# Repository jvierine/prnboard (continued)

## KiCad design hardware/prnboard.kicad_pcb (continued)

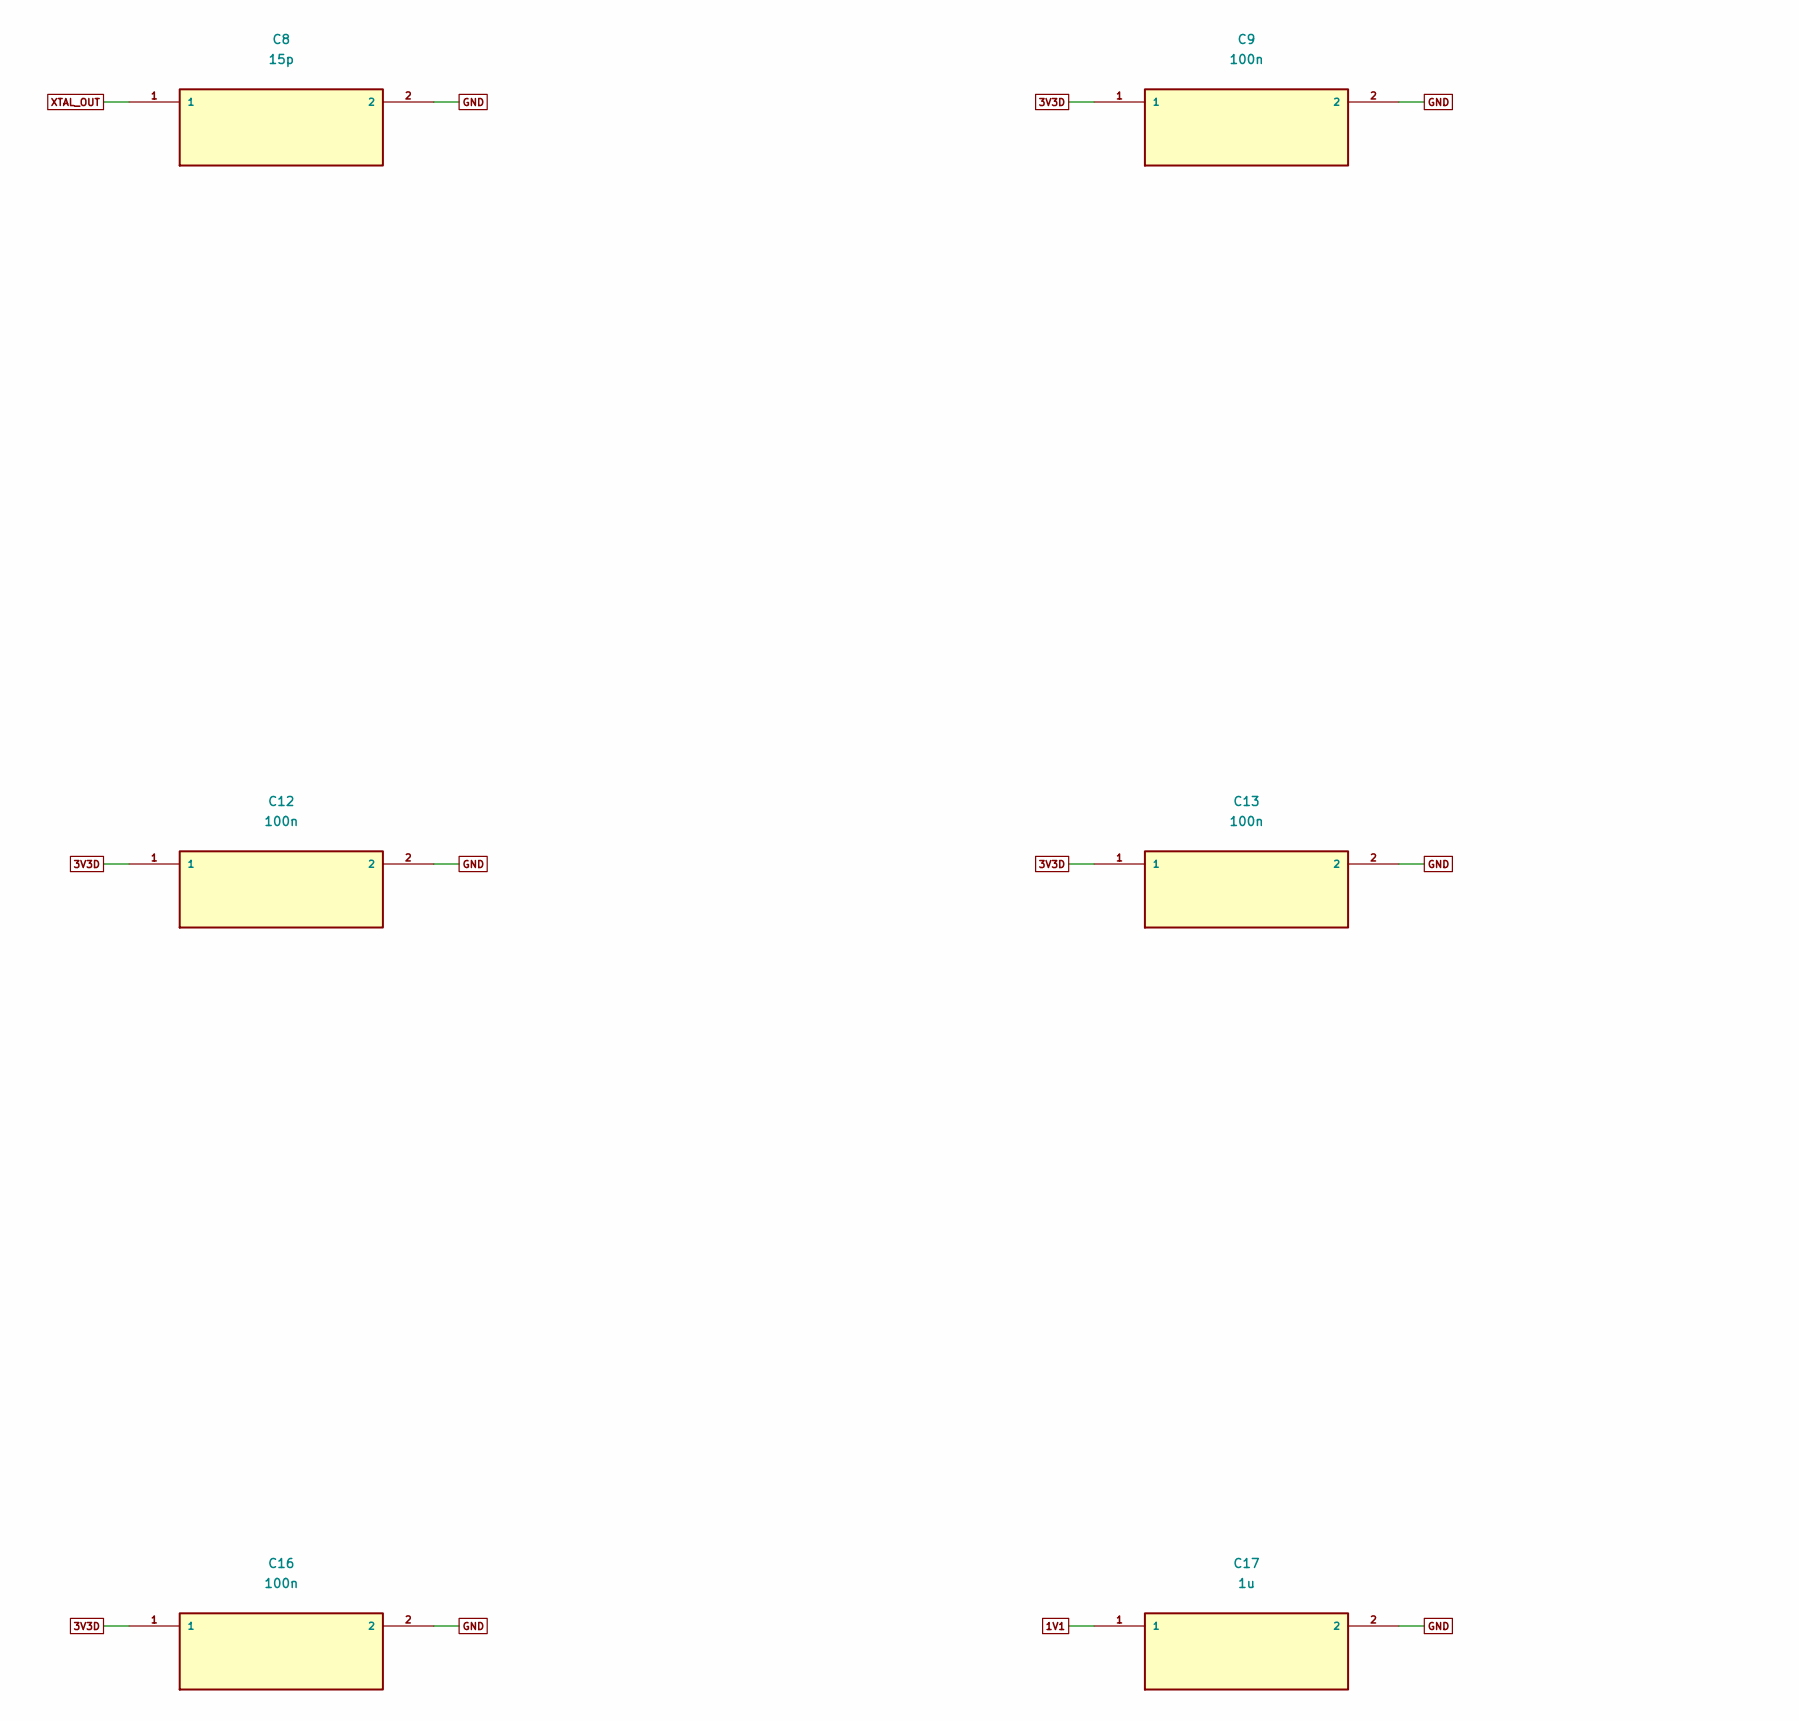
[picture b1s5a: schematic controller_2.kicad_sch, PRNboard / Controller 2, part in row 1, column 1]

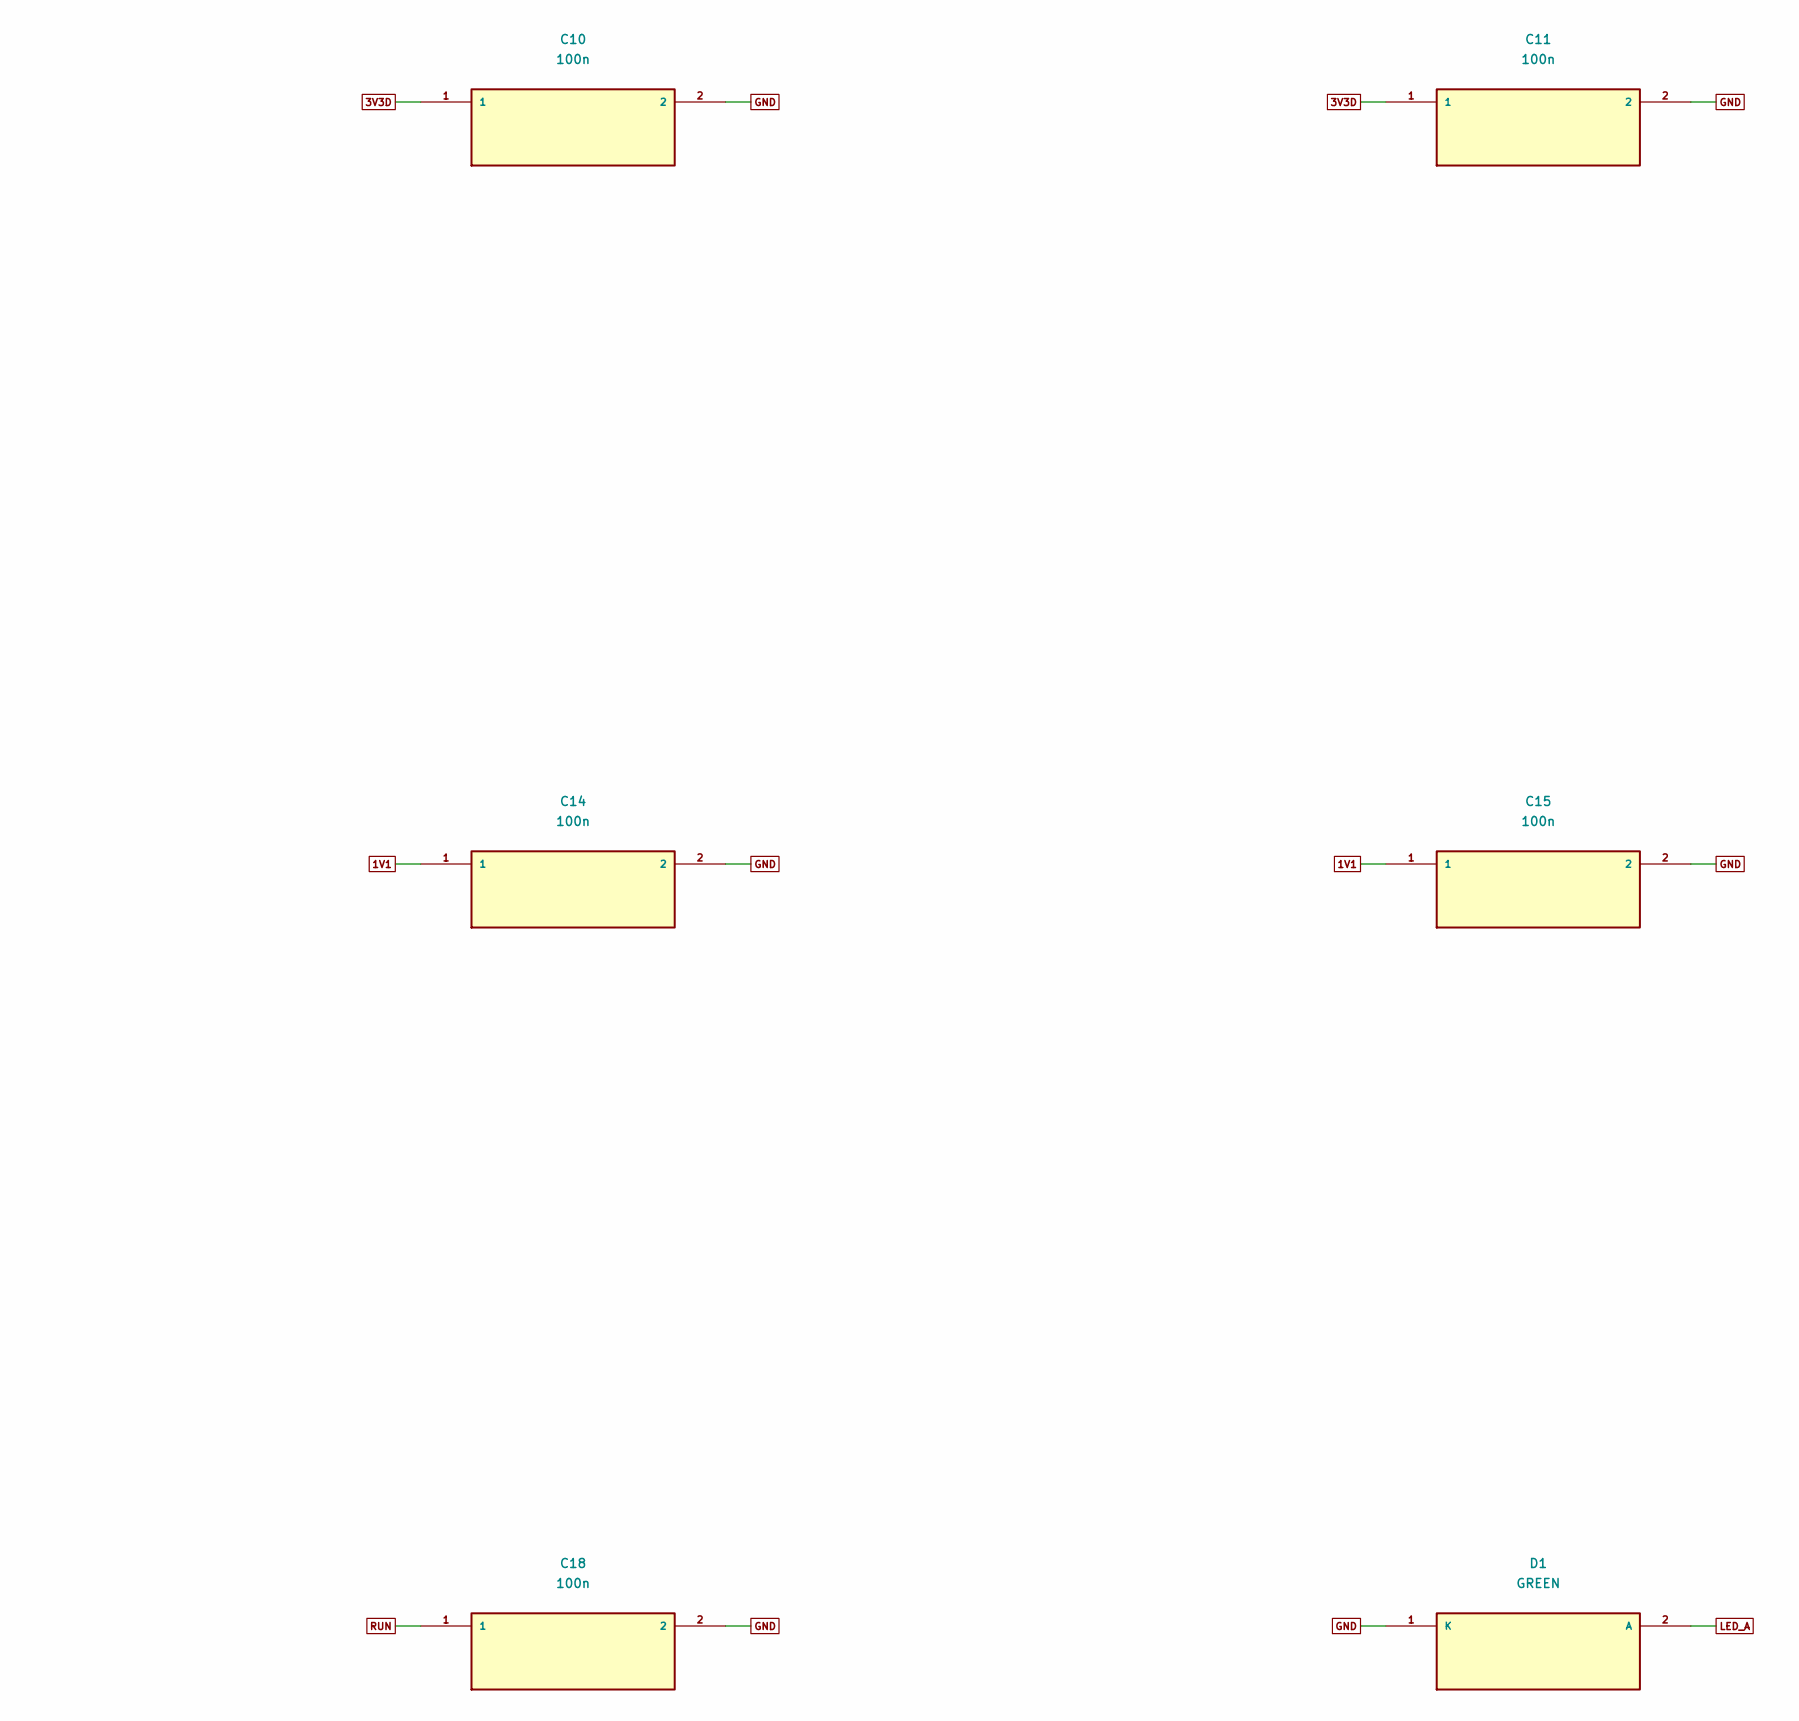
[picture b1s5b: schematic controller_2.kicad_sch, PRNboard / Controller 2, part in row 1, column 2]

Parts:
C8: 15p; C8; MPN SELECT_IN_BOM
C9: 100n; C9; MPN SELECT_IN_BOM
C10: 100n; C10; MPN SELECT_IN_BOM
C11: 100n; C11; MPN SELECT_IN_BOM
C12: 100n; C12; MPN SELECT_IN_BOM
C13: 100n; C13; MPN SELECT_IN_BOM
C14: 100n; C14; MPN SELECT_IN_BOM
C15: 100n; C15; MPN SELECT_IN_BOM
C16: 100n; C16; MPN SELECT_IN_BOM
C17: 1u; C17; MPN SELECT_IN_BOM
C18: 100n; C18; MPN SELECT_IN_BOM
D1: GREEN; D1; MPN GREEN

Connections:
1V1: C14.1, C15.1, C17.1; also elsewhere on the board
3V3D: C9.1, C10.1, C11.1, C12.1, C13.1, C16.1; also elsewhere on the board
GND: C8.2, C9.2, C10.2, C11.2, C12.2, C13.2, C14.2, C15.2, C16.2, C17.2, C18.2, D1.1 (K); also elsewhere on the board
LED_A: D1.2 (A); also elsewhere on the board
RUN: C18.1; also elsewhere on the board
XTAL_OUT: C8.1; also elsewhere on the board

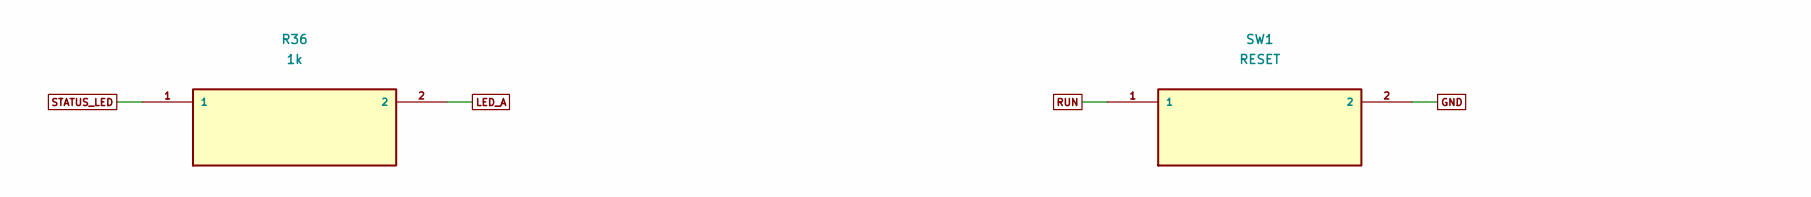
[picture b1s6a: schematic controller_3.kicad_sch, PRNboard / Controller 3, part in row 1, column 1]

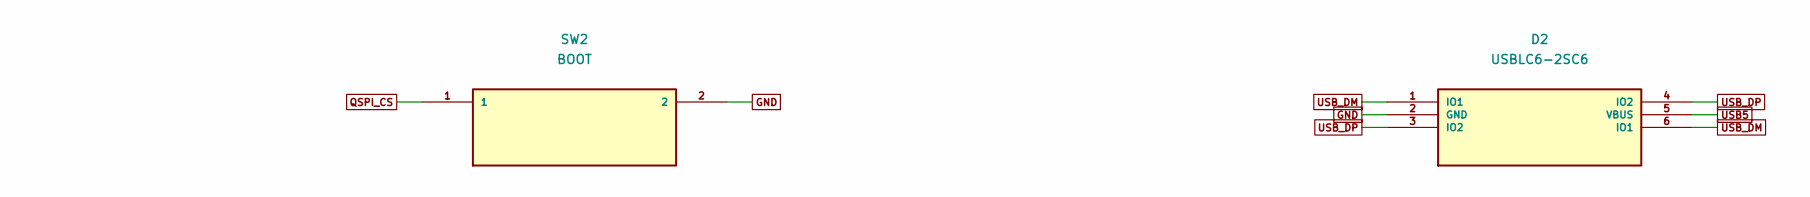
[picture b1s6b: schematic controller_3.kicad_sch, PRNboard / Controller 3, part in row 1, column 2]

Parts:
D2: USBLC6-2SC6; D2; MPN USBLC6-2SC6; LCSC C7519
R36: 1k; R36; MPN SELECT_IN_BOM
SW1: RESET; SW1; MPN TL3342F160QG
SW2: BOOT; SW2; MPN TL3342F160QG

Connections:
GND: D2.2 (GND), SW1.2, SW2.2; also elsewhere on the board
LED_A: R36.2; also elsewhere on the board
QSPI_CS: SW2.1; also elsewhere on the board
RUN: SW1.1; also elsewhere on the board
STATUS_LED: R36.1; also elsewhere on the board
USB5: D2.5 (VBUS); also elsewhere on the board
USB_DM: D2.1 (IO1), D2.6 (IO1); also elsewhere on the board
USB_DP: D2.3 (IO2), D2.4 (IO2); also elsewhere on the board

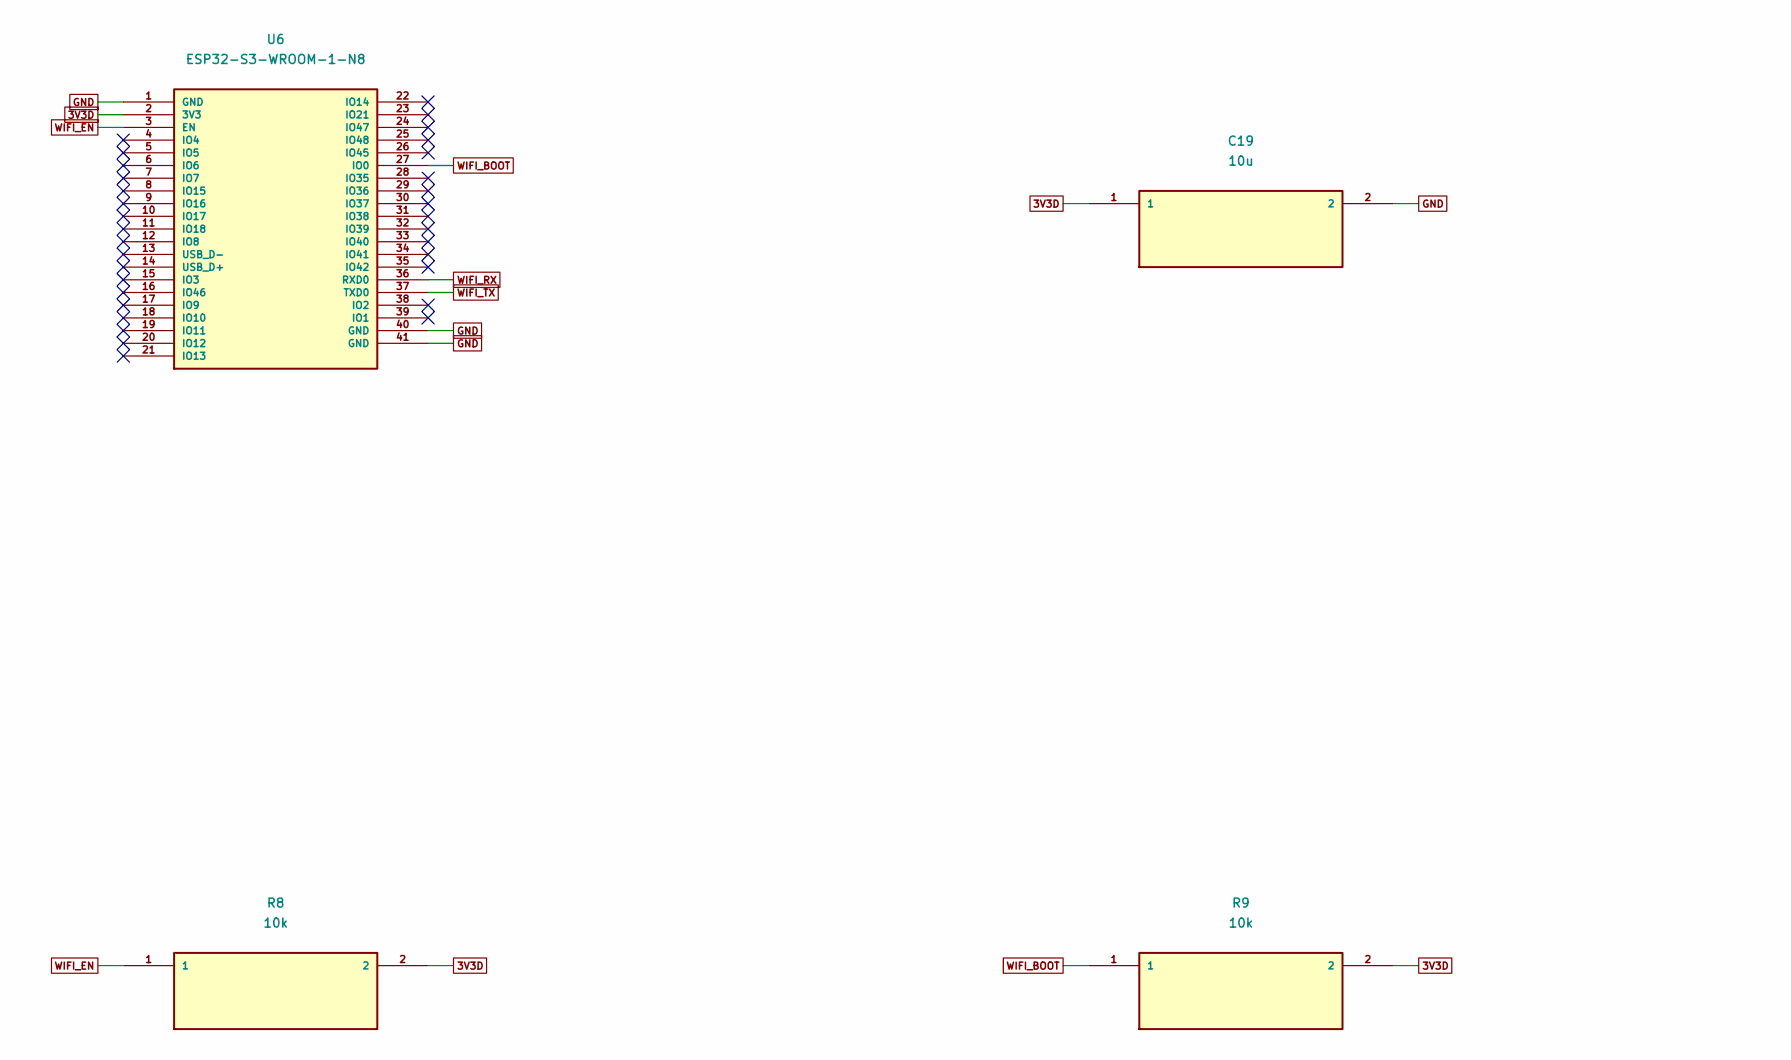
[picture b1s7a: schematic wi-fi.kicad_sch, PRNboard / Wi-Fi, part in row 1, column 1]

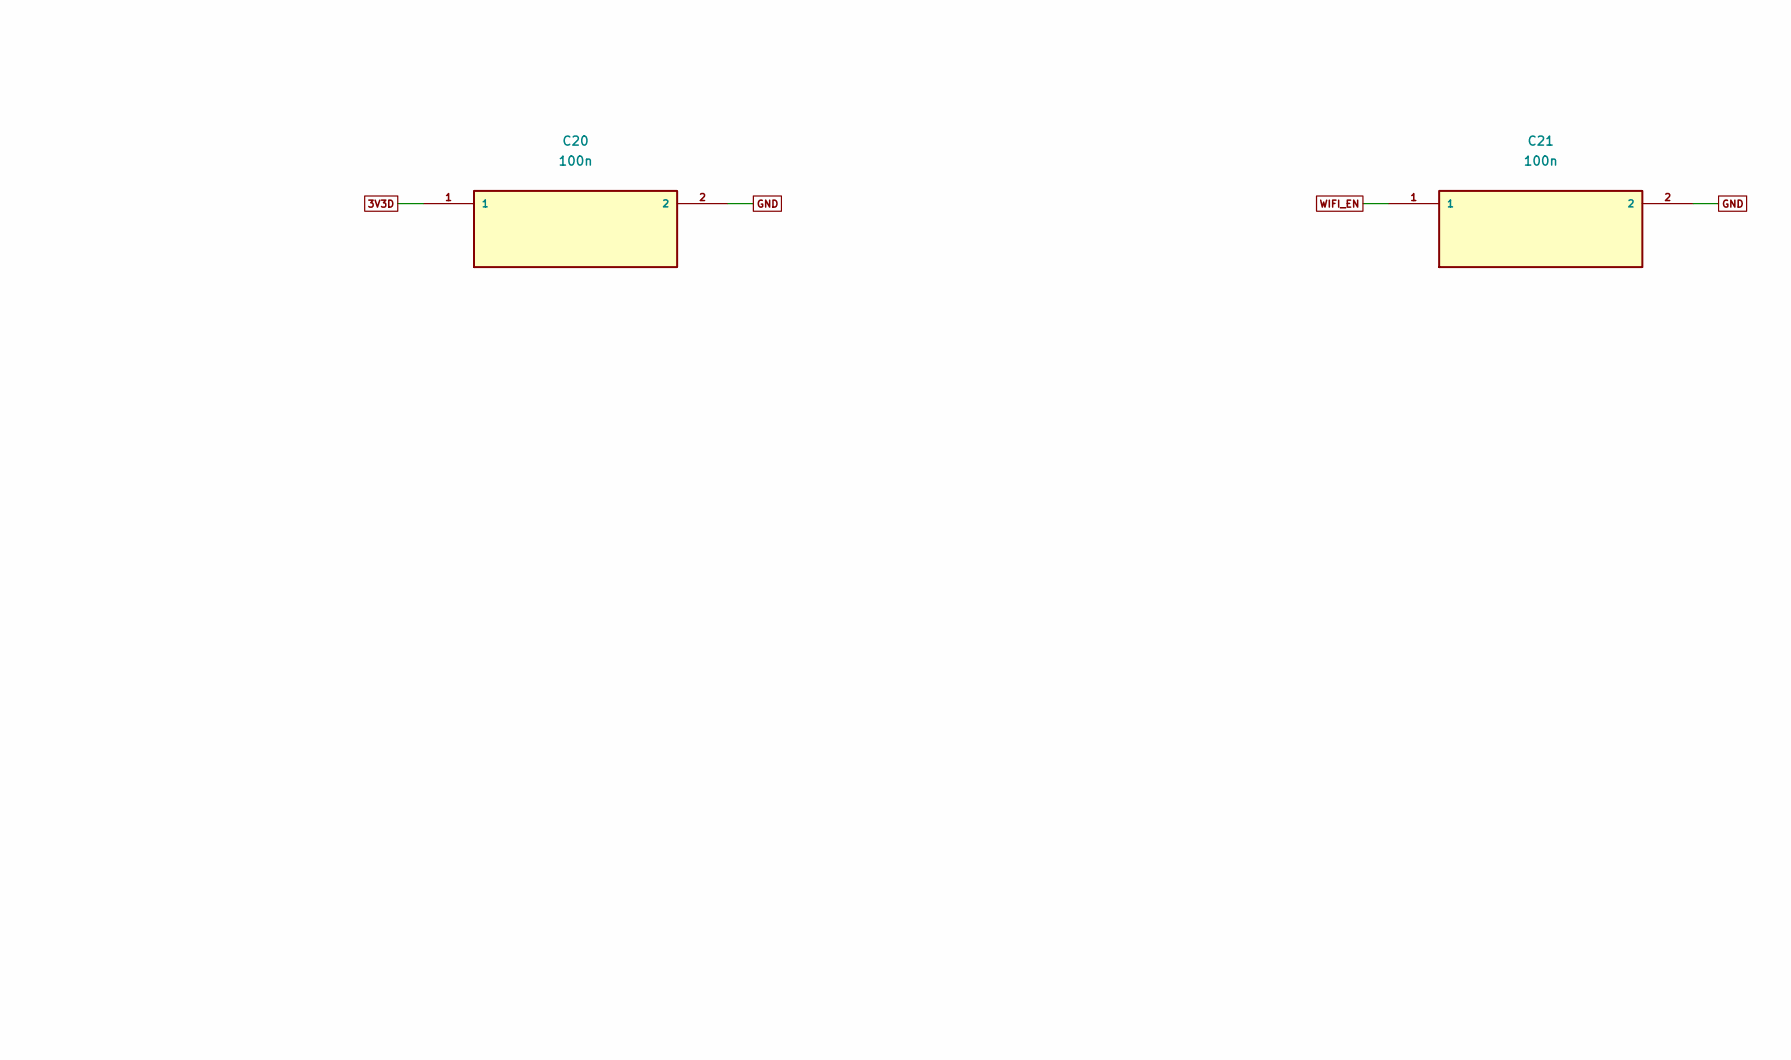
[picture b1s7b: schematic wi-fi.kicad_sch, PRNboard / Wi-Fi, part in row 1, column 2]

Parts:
C19: 10u; C19; MPN SELECT_IN_BOM
C20: 100n; C20; MPN SELECT_IN_BOM
C21: 100n; C21; MPN SELECT_IN_BOM
R8: 10k; R8; MPN SELECT_IN_BOM
R9: 10k; R9; MPN SELECT_IN_BOM
U6: ESP32-S3-WROOM-1-N8; U6; MPN ESP32-S3-WROOM-1-N8; LCSC C2913198

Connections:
3V3D: C19.1, C20.1, R8.2, R9.2, U6.2 (3V3); also elsewhere on the board
GND: C19.2, C20.2, C21.2, U6.1 (GND), U6.40 (GND), U6.41 (GND); also elsewhere on the board
WIFI_BOOT: R9.1, U6.27 (IO0); also elsewhere on the board
WIFI_EN: C21.1, R8.1, U6.3 (EN); also elsewhere on the board
WIFI_RX: U6.36 (RXD0); also elsewhere on the board
WIFI_TX: U6.37 (TXD0); also elsewhere on the board

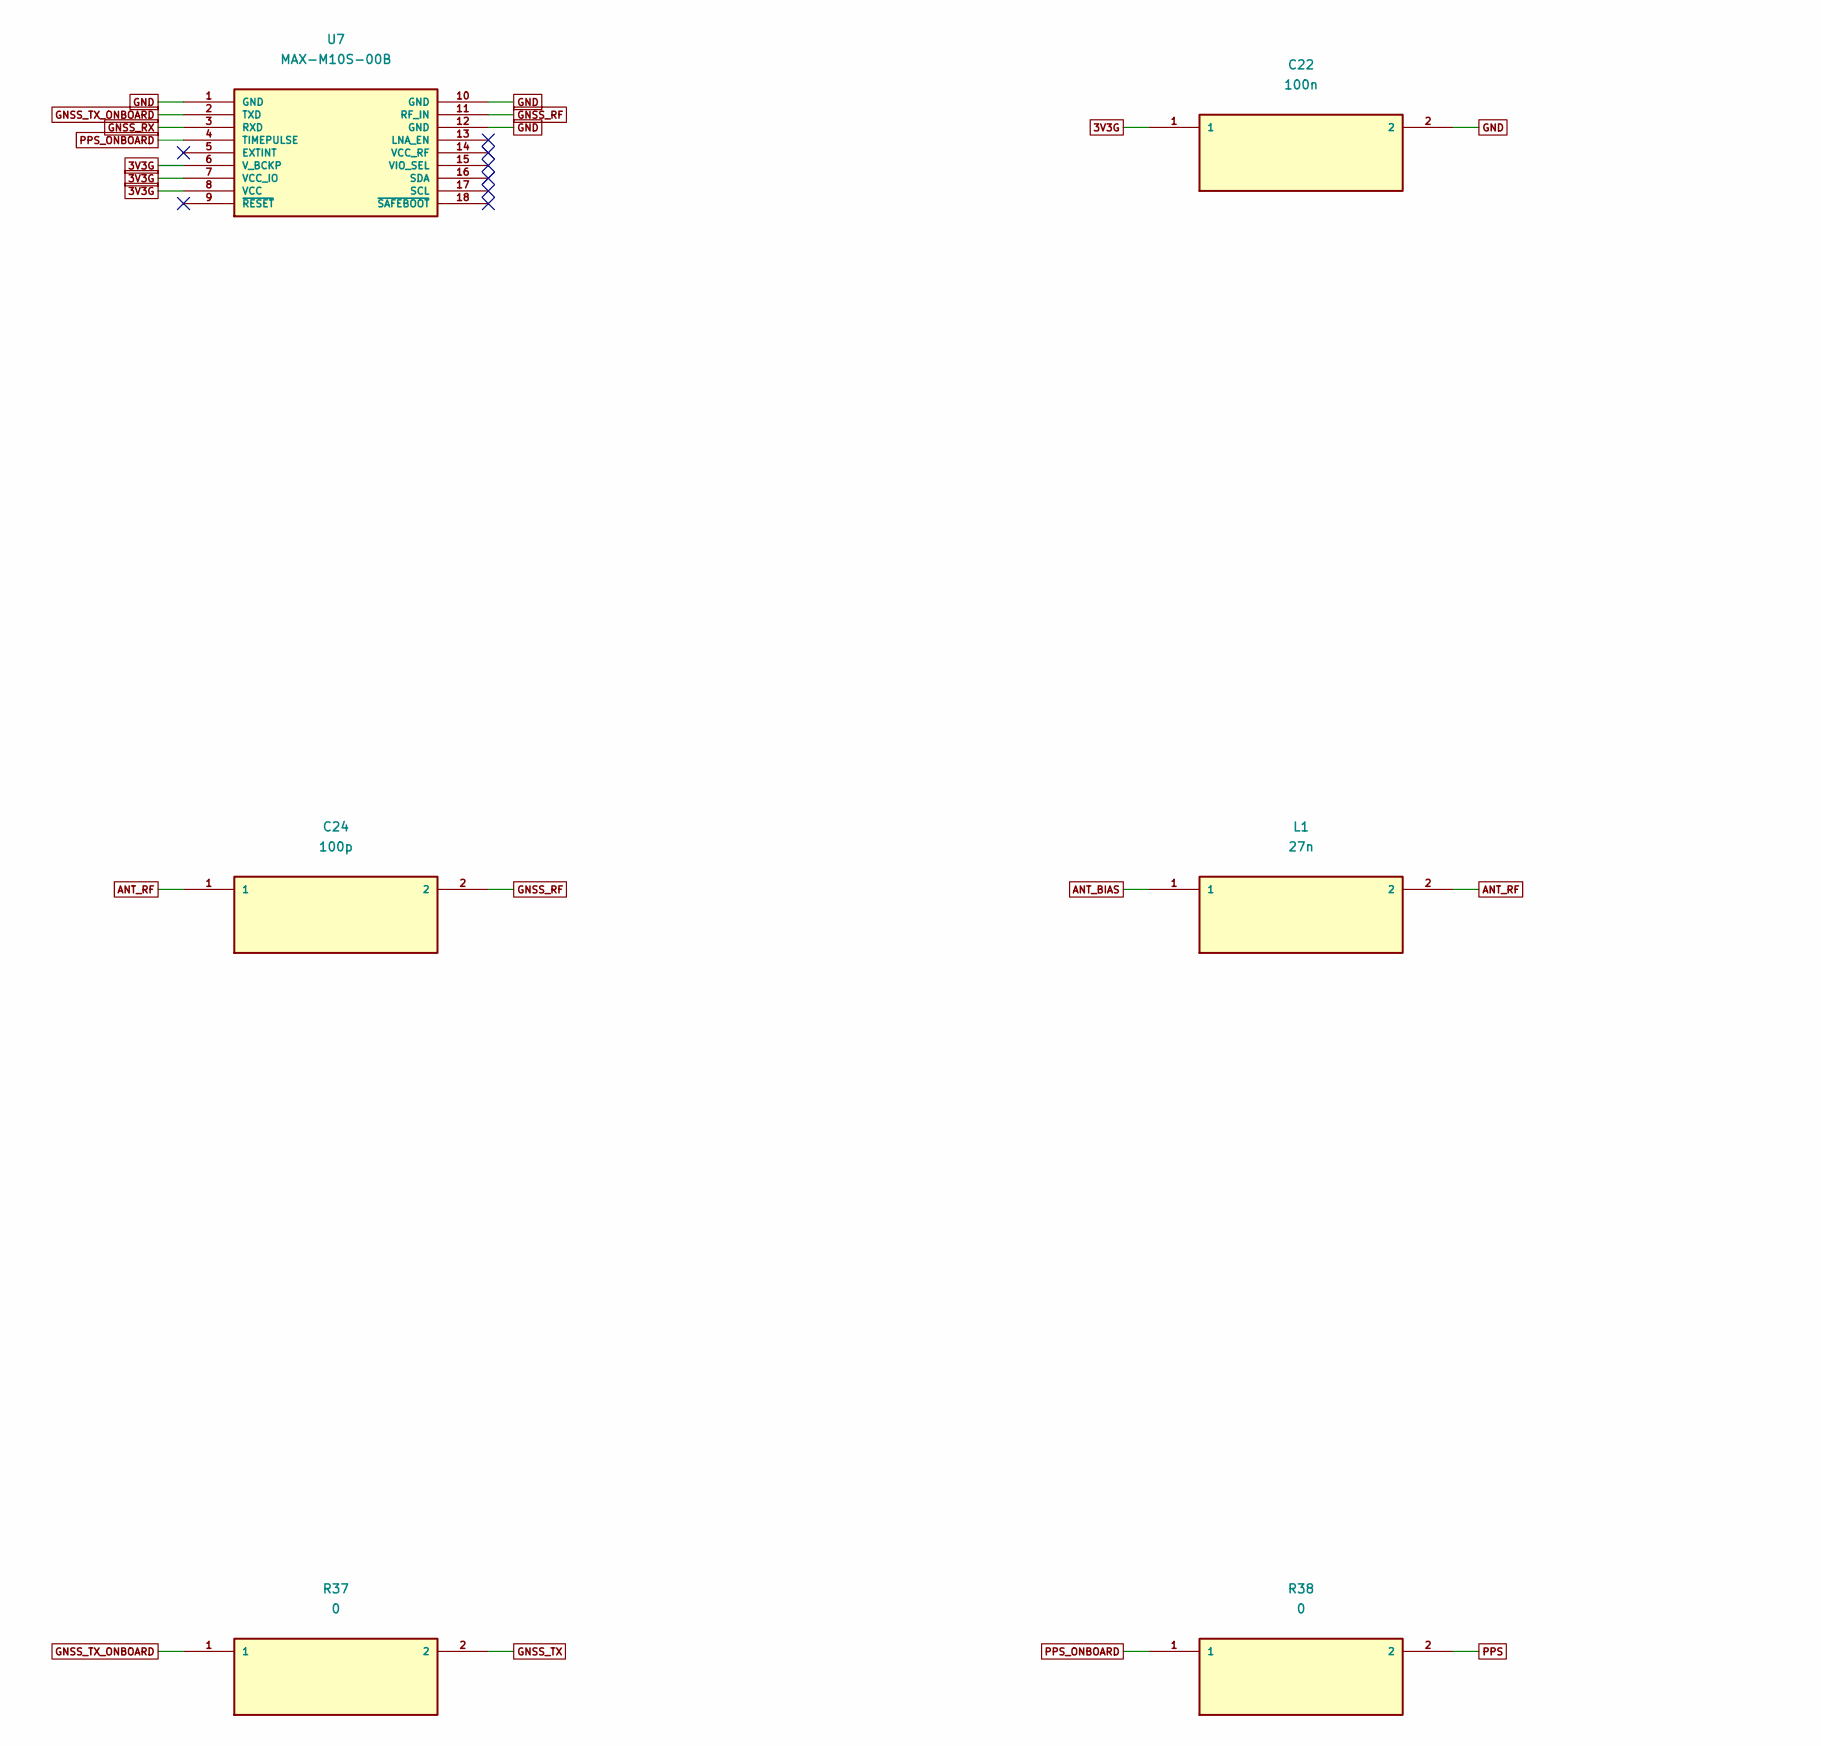
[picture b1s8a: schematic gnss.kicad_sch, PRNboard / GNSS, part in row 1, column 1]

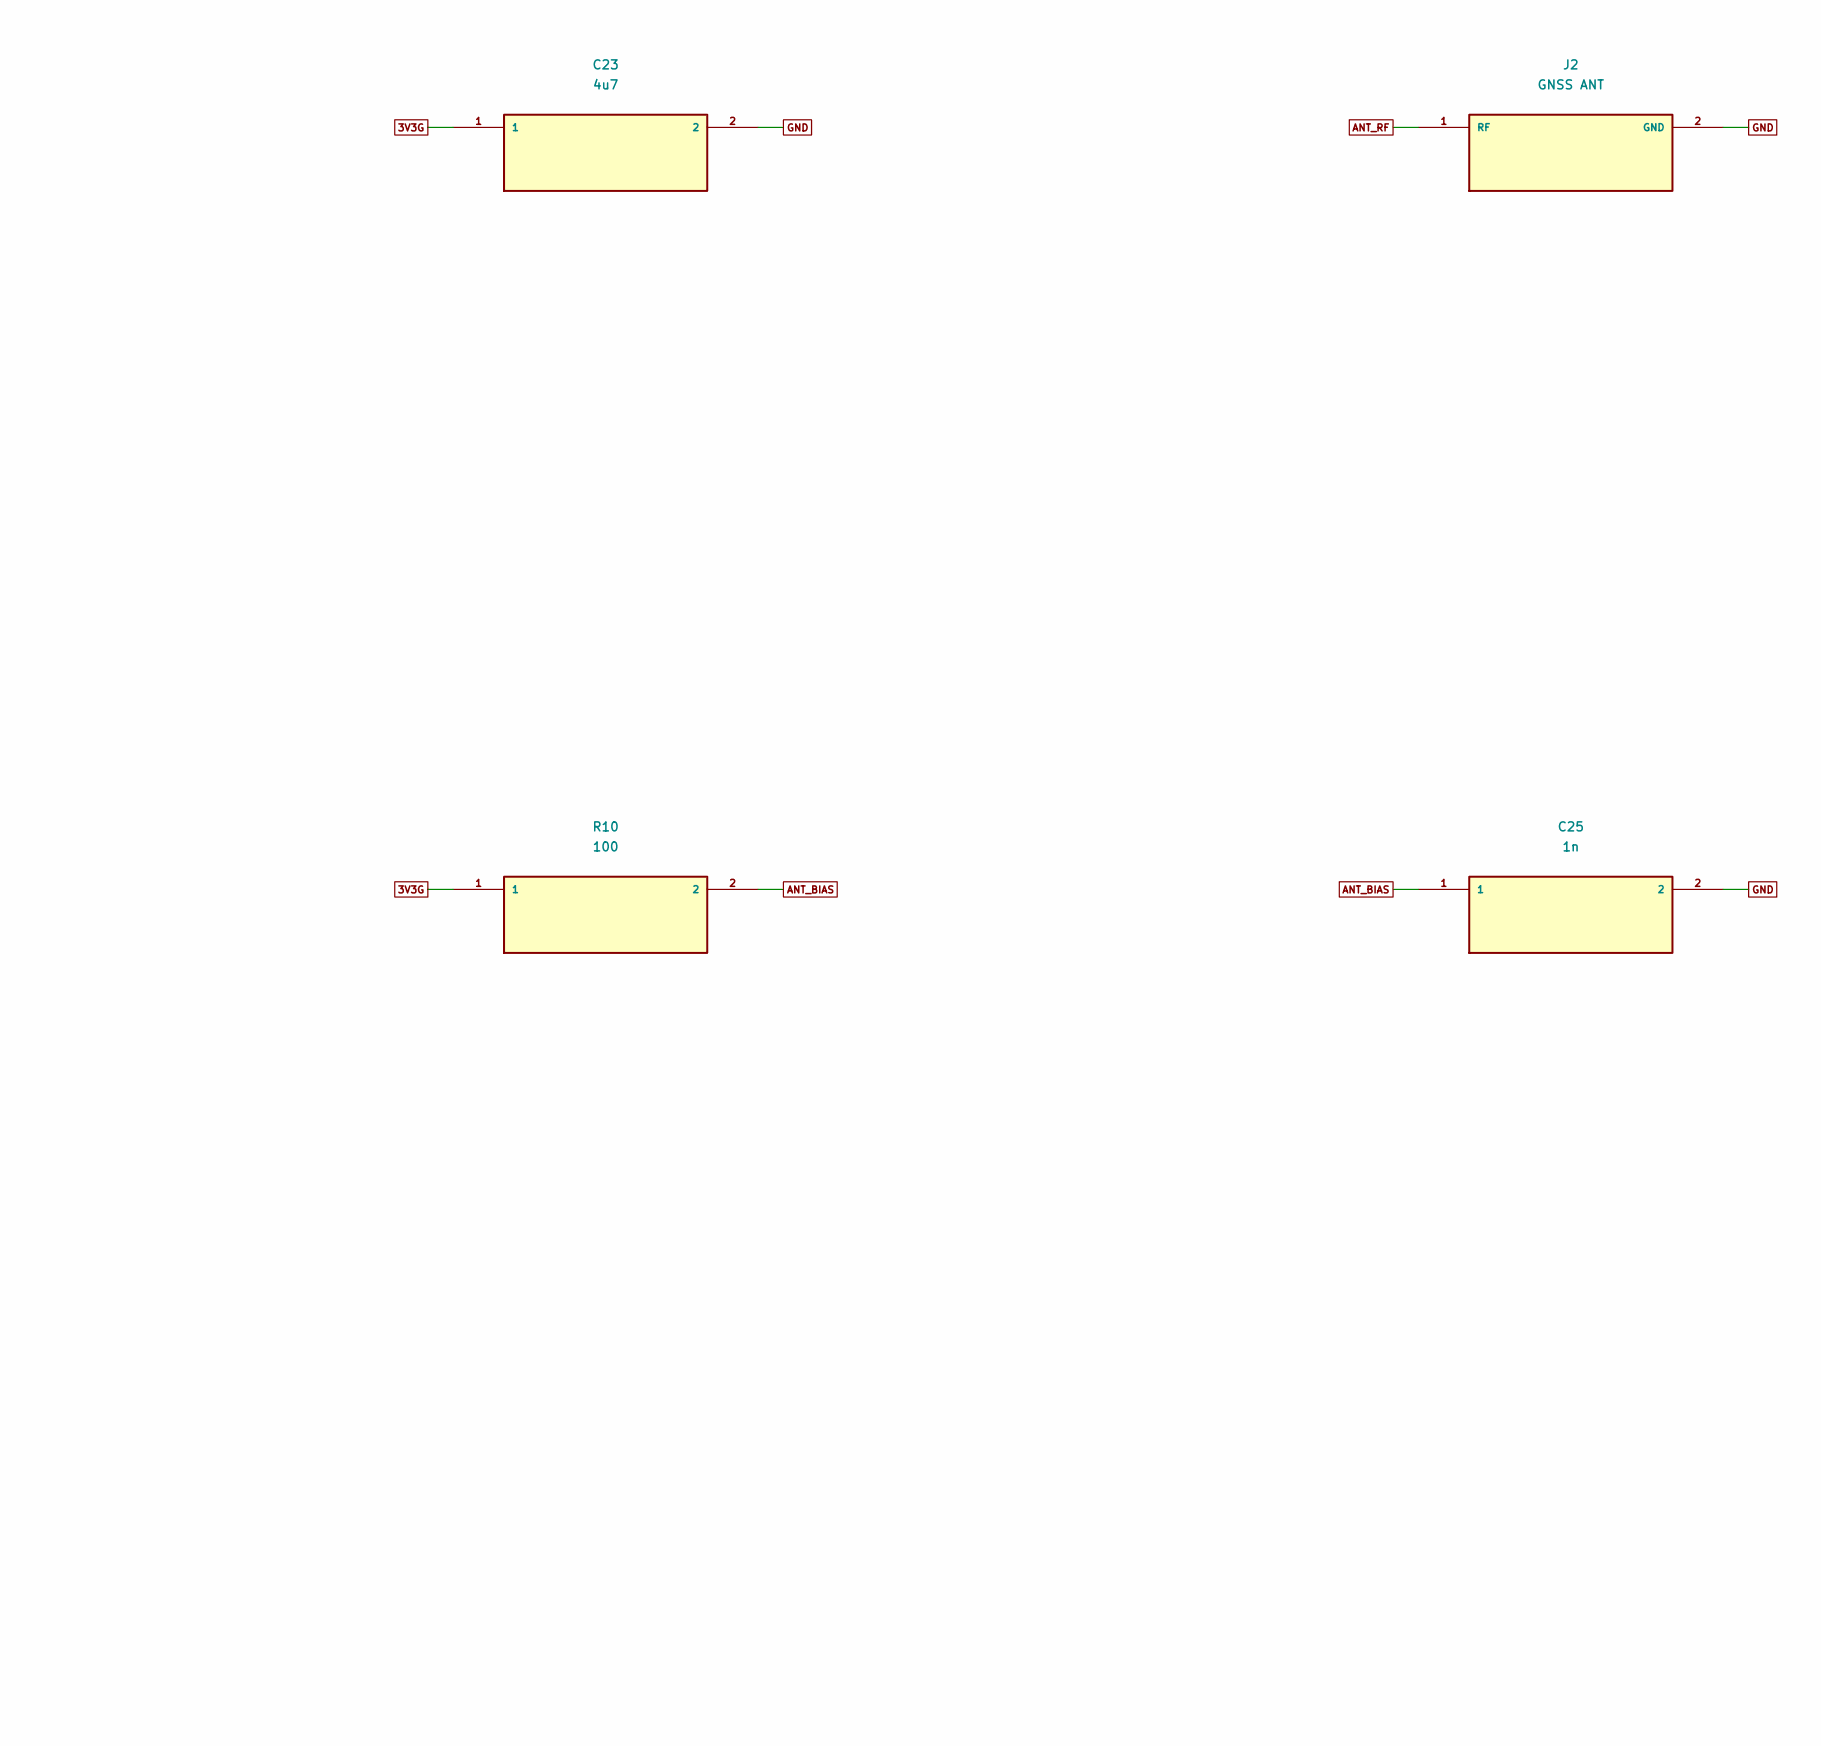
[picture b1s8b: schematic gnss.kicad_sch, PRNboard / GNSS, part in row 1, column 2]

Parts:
C22: 100n; C22; MPN SELECT_IN_BOM
C23: 4u7; C23; MPN SELECT_IN_BOM
C24: 100p; C24; MPN SELECT_IN_BOM
C25: 1n; C25; MPN SELECT_IN_BOM
J2: GNSS ANT; J2; MPN 132134
L1: 27n; L1; MPN SELECT_IN_BOM
R10: 100; R10; MPN SELECT_IN_BOM
R37: 0; R37; MPN SELECT_IN_BOM
R38: 0; R38; MPN SELECT_IN_BOM
U7: MAX-M10S-00B; U7; MPN MAX-M10S-00B; LCSC C4153167

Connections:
3V3G: C22.1, C23.1, R10.1, U7.6 (V_BCKP), U7.7 (VCC_IO), U7.8 (VCC); also elsewhere on the board
ANT_BIAS: C25.1, L1.1, R10.2
ANT_RF: C24.1, J2.1 (RF), L1.2
GND: C22.2, C23.2, C25.2, J2.2 (GND), U7.1 (GND), U7.10 (GND), U7.12 (GND); also elsewhere on the board
GNSS_RF: C24.2, U7.11 (RF_IN)
GNSS_RX: U7.3 (RXD); also elsewhere on the board
GNSS_TX: R37.2; also elsewhere on the board
GNSS_TX_ONBOARD: R37.1, U7.2 (TXD)
PPS: R38.2; also elsewhere on the board
PPS_ONBOARD: R38.1, U7.4 (TIMEPULSE)

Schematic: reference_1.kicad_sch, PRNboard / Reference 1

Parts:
C26: 4u7; C26; MPN SELECT_IN_BOM
C27: 4u7; C27; MPN SELECT_IN_BOM
C28: 100n; C28; MPN SELECT_IN_BOM
C29: 1n; C29; MPN SELECT_IN_BOM
C30: 4u7; C30; MPN SELECT_IN_BOM
R11: 1k; R11; MPN SELECT_IN_BOM
R12: 1k; R12; MPN SELECT_IN_BOM
R13: 10k; R13; MPN SELECT_IN_BOM
R14: 10k; R14; MPN SELECT_IN_BOM
R15: 10k; R15; MPN SELECT_IN_BOM
U8: MCP4725A1T-E/CH; U8; MPN MCP4725A1T-E/CH; LCSC C61423
Y2: 10MHz VCTCXO; Y2; MPN 1XTV10000MDA; LCSC C253701

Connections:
3V3RF: C28.1, R13.1, U8.3 (VDD), Y2.4 (VCC); also elsewhere on the board
DAC: R11.1, U8.1 (VOUT)
DAC_FILTER: C26.1, R11.2, R12.1
GND: C26.2, C27.2, C28.2, C30.2, R14.2, U8.2 (VSS), U8.6 (A0), Y2.2 (GND); also elsewhere on the board
I2C_SCL: U8.5 (SCL); also elsewhere on the board
I2C_SDA: U8.4 (SDA); also elsewhere on the board
MID: C30.1, R13.2, R14.1, R15.1; also elsewhere on the board
OSC_SINE: C29.1, Y2.3 (OUT)
SINE_AC: C29.2, R15.2; also elsewhere on the board
VCTRL: C27.1, R12.2, Y2.1 (VC)

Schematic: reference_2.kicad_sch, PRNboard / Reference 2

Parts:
C31: 100n; C31; MPN SELECT_IN_BOM
C32: 100n; C32; MPN SELECT_IN_BOM
C37: 100n; C37; MPN SELECT_IN_BOM
R16: 1k; R16; MPN SELECT_IN_BOM
R17: 1k; R17; MPN SELECT_IN_BOM
R18: 330; R18; MPN SELECT_IN_BOM
R19: 100; R19; MPN SELECT_IN_BOM
U9: TLV3501AIDBVR; U9; MPN TLV3501AIDBVR

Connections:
3V3D: R16.2, R17.2; also elsewhere on the board
3V3RF: C31.1, C32.1, U9.4 (VCC); also elsewhere on the board
DDS_REF: C37.2; also elsewhere on the board
GND: C31.2, C32.2, R19.2, U9.2 (GND), U9.6 (SHDN); also elsewhere on the board
I2C_SCL: R17.1; also elsewhere on the board
I2C_SDA: R16.1; also elsewhere on the board
MID: U9.1 (IN-); also elsewhere on the board
REF10: R18.1, U9.5 (OUT); also elsewhere on the board
REF_ATT: C37.1, R18.2, R19.1
SINE_AC: U9.3 (IN+); also elsewhere on the board

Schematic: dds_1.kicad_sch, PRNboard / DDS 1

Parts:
C54: 100n; C54; MPN SELECT_IN_BOM
C55: 10n; C55; MPN SELECT_IN_BOM
C56: 100n; C56; MPN SELECT_IN_BOM
C57: 100n; C57; MPN SELECT_IN_BOM
C58: 100n; C58; MPN SELECT_IN_BOM
C59: 100n; C59; MPN SELECT_IN_BOM
C60: 100n; C60; MPN SELECT_IN_BOM
R20: 243; R20; MPN SELECT_IN_BOM
R21: 3k92; R21; MPN SELECT_IN_BOM
R22: 49R9; R22; MPN SELECT_IN_BOM
R23: 49R9; R23; MPN SELECT_IN_BOM
U11: AD9954YSVZ-REEL7; U11; MPN AD9954YSVZ-REEL7; LCSC C496484

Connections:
1V8A: C54.2, C56.1, C57.1, C58.1, C59.1, C60.1, R22.2, R23.2, U11.4 (AVDD), U11.6 (AVDD), U11.13 (AVDD), U11.16 (AVDD), U11.18 (AVDD), U11.19 (AVDD), U11.25 (AVDD), U11.27 (AVDD), U11.29 (AVDD); also elsewhere on the board
1V8D: U11.2 (DVDD), U11.34 (DVDD); also elsewhere on the board
3V3D: U11.43 (DVDD_I/O); also elsewhere on the board
DAC_A: R23.1, U11.21 (IOUT); also elsewhere on the board
DAC_B: R22.1, U11.20 (~IOUT)
DAC_BP: U11.23 (DACBP); also elsewhere on the board
DDS_CS_N: U11.39 (~CS); also elsewhere on the board
DDS_DATA: U11.41 (SDIO); also elsewhere on the board
DDS_PLL: R20.1, U11.12 (LOOP_FILTER)
DDS_PS0: U11.47 (PS0); also elsewhere on the board
DDS_REF: U11.9 (OSC/REFCLK); also elsewhere on the board
DDS_RESET: U11.36 (RESET); also elsewhere on the board
DDS_SDO: U11.38 (SDO); also elsewhere on the board
DDS_SYNC_CLK: U11.45 (SYNC_CLK); also elsewhere on the board
DDS_UPDATE: U11.1 (I/OUPDATE); also elsewhere on the board
DDS_WCLK: U11.40 (SCLK); also elsewhere on the board
GND: C55.2, C56.2, C57.2, C58.2, C59.2, C60.2, R21.2, U11.3 (DGND), U11.5 (AGND), U11.7 (AGND), U11.11 (CLKMODESELECT), U11.14 (AGND), U11.15 (AGND), U11.17 (AGND), U11.22 (AGND), U11.26 (AGND), U11.30 (COMP_IN), U11.31 (~COMP_IN), U11.32 (AGND), U11.33 (DGND), U11.35 (PWRDWNCTL), U11.37 (IOSYNC), U11.42 (DGND), U11.44 (SYNC_IN), U11.46 (OSK), U11.48 (PS1), U11.49 (AGND); also elsewhere on the board
PLL_RC: C55.1, R20.2
REF_N: C54.1, U11.8 (~OSC/REFCLK)
RSET: R21.1, U11.24 (DAC_R_{SET})

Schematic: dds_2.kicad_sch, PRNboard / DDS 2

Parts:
C38: 100n; C38; MPN SELECT_IN_BOM
C61: 100n; C61; MPN SELECT_IN_BOM
C62: 100n; C62; MPN SELECT_IN_BOM
C63: 100n; C63; MPN SELECT_IN_BOM
C64: 100n; C64; MPN SELECT_IN_BOM
C65: 100n; C65; MPN SELECT_IN_BOM
C66: 100n; C66; MPN SELECT_IN_BOM
C67: 100n; C67; MPN SELECT_IN_BOM
R39: 10k; R39; MPN SELECT_IN_BOM
R40: 10k; R40; MPN SELECT_IN_BOM

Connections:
1V8A: C61.1, C62.1, C63.1, C64.1; also elsewhere on the board
1V8D: C65.1, C66.1; also elsewhere on the board
3V3D: C67.1, R39.2; also elsewhere on the board
DAC_BP: C38.1; also elsewhere on the board
DDS_CS_N: R39.1; also elsewhere on the board
DDS_PS0: R40.1; also elsewhere on the board
GND: C38.2, C61.2, C62.2, C63.2, C64.2, C65.2, C66.2, C67.2, R40.2; also elsewhere on the board

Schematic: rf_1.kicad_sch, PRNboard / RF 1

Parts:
C42: 110p; C42; MPN SELECT_IN_BOM
C43: 180p; C43; MPN SELECT_IN_BOM
C44: 110p; C44; MPN SELECT_IN_BOM
C45: 100n; C45; MPN SELECT_IN_BOM
L2: 100n; L2; MPN SELECT_IN_BOM
L3: 390n; L3; MPN SELECT_IN_BOM
L4: 390n; L4; MPN SELECT_IN_BOM
L5: 100n; L5; MPN SELECT_IN_BOM
R24: 49R9; R24; MPN SELECT_IN_BOM
R25: 10k; R25; MPN SELECT_IN_BOM
U12: TS5A3159DBVR; U12; MPN TS5A3159DBVR
U13: OPA356AIDBVR; U13; MPN OPA356AIDBVR

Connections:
1V8A: R24.2; also elsewhere on the board
3V3RF: U12.5 (V+), U13.5 (V+); also elsewhere on the board
AMP_FB: U13.4 (-); also elsewhere on the board
AMP_IN: U12.3, U13.3 (+)
AMP_OUT: U13.1; also elsewhere on the board
DAC_A: L2.1; also elsewhere on the board
GND: C42.2, C43.2, C44.2, U12.2 (GND), U13.2 (V-); also elsewhere on the board
LP1: C42.1, L2.2, L3.1
LP2: C43.1, L3.2, L4.1
LP3: C44.1, L4.2, L5.1
LP_OUT: C45.1, L5.2, R24.1
MID: R25.2, U12.4; also elsewhere on the board
RF_IN_AC: C45.2, R25.1, U12.1
TX_ENABLE: U12.6; also elsewhere on the board

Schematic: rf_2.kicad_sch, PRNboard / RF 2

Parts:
C46: 100n; C46; MPN SELECT_IN_BOM
C47: 100n; C47; MPN SELECT_IN_BOM
C48: 100n; C48; MPN SELECT_IN_BOM
J3: EXCITER OUT; J3; MPN 132134
R26: 300; R26; MPN SELECT_IN_BOM
R27: 100; R27; MPN SELECT_IN_BOM
R28: 49R9; R28; MPN SELECT_IN_BOM

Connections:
3V3RF: C47.1, C48.1; also elsewhere on the board
AMP_FB: R26.2, R27.1; also elsewhere on the board
AMP_OUT: R26.1, R28.1; also elsewhere on the board
GND: C47.2, C48.2, J3.2 (GND); also elsewhere on the board
MID: R27.2; also elsewhere on the board
RF_OUT: C46.2, J3.1 (RF)
RF_SERIES: C46.1, R28.2
